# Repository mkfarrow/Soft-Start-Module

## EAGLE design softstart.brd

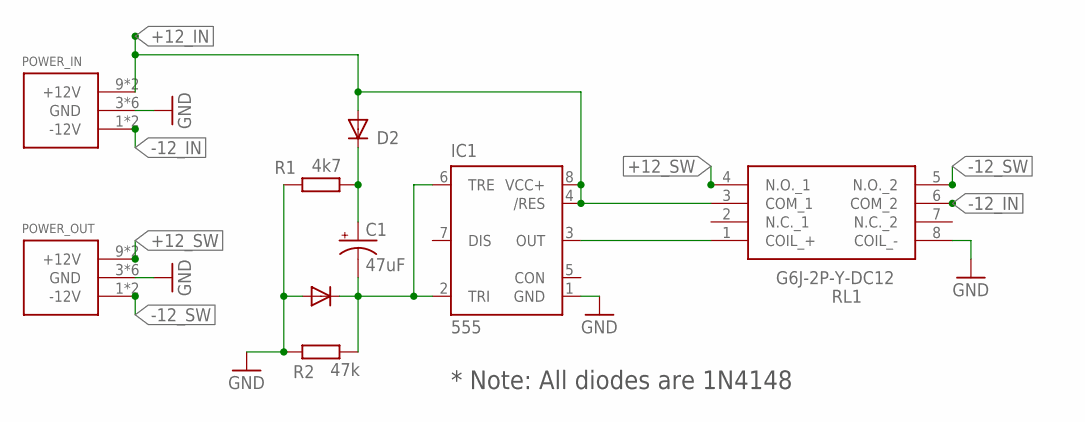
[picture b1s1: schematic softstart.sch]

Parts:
C1: 47uF; TT2D6
D1: 1N4001; SMALL_DIODE
D2: SMALL_DIODEDO35-7; SMALL_DIODE
IC1: 555; DIP08
POWER_IN: RUSS_EURORACK_POWER_SIMPLE10; RUSS_EURORACK_POWER_10
POWER_OUT: RUSS_EURORACK_POWER_SIMPLE10; RUSS_EURORACK_POWER_10
R1: 4k7; 7MM_RESISTOR
R2: 47k; 7MM_RESISTOR
RL1: G6J-2P-Y-DC12; G6J2PYDC12

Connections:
+12_IN: D2.A, IC1.4 (/RES), IC1.8 (VCC+), POWER_IN.9 (+12V), POWER_IN.10 (+12V), RL1.3 (COM_1)
+12_SW: POWER_OUT.9 (+12V), POWER_OUT.10 (+12V), RL1.4 (N.O._1)
-12_IN: POWER_IN.1 (-12V), POWER_IN.2 (-12V), RL1.6 (COM_2)
-12_SW: POWER_OUT.1 (-12V), POWER_OUT.2 (-12V), RL1.5 (N.O._2)
GND: D1.A, IC1.1 (GND), POWER_IN.3 (GND), POWER_IN.4 (GND), POWER_IN.5 (GND), POWER_IN.6 (GND), POWER_IN.7 (GND), POWER_IN.8 (GND), POWER_OUT.3 (GND), POWER_OUT.4 (GND), POWER_OUT.5 (GND), POWER_OUT.6 (GND), POWER_OUT.7 (GND), POWER_OUT.8 (GND), R1.1, R2.1, RL1.8 (COIL_-)
unnamed: C1.+, D2.C, R1.2
unnamed: C1.-, D1.C, IC1.2 (TRI), IC1.6 (TRE), R2.2
unnamed: IC1.3 (OUT), RL1.1 (COIL_+)

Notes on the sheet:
* Note: All diodes are 1N4148

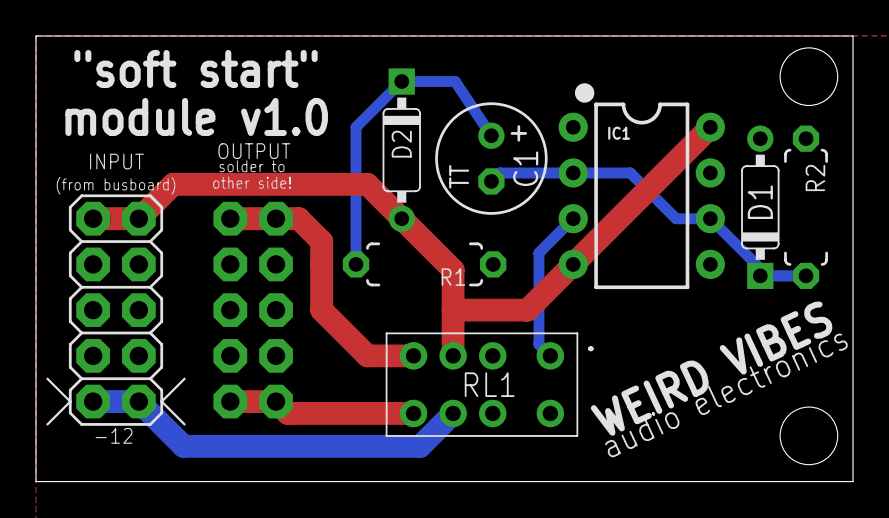
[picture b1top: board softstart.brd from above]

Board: 2 copper layers, 45.4 x 24.8 mm, 9 parts (1 on the bottom side), 8 nets.

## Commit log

2023-02-22 added gerbers

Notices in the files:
parts and their libraries:
SparkFun-IC-Special-Function: Licensing: Creative Commons ShareAlike 4.0 International - https://creativecommons.org/licenses/by-sa/4.0
